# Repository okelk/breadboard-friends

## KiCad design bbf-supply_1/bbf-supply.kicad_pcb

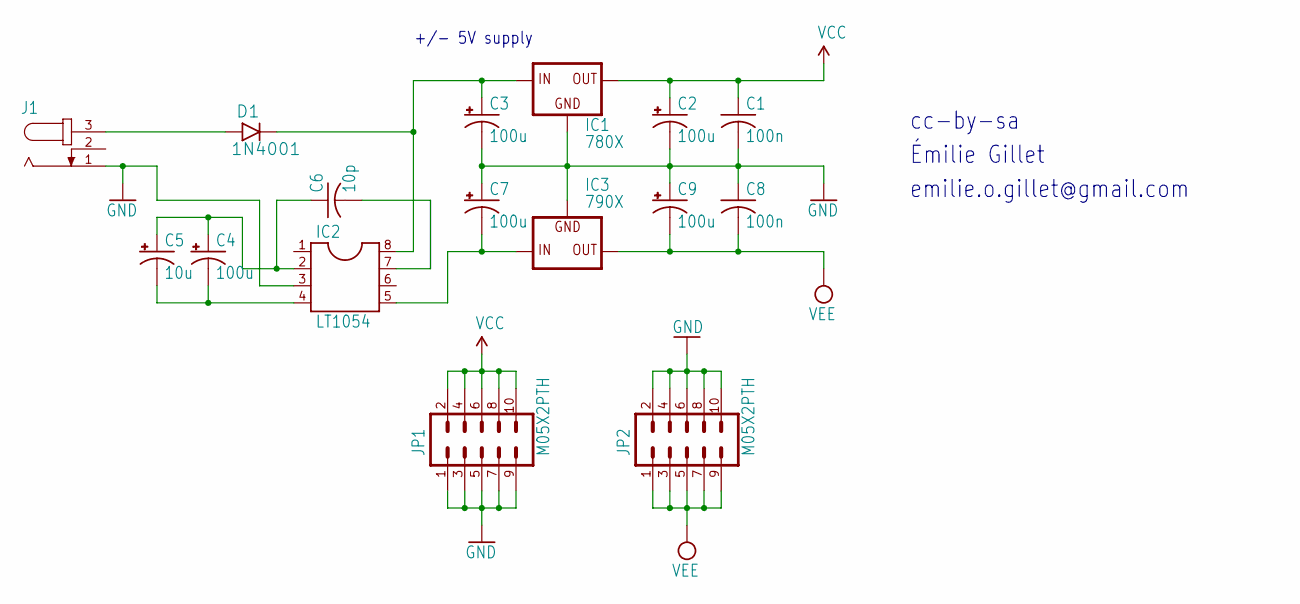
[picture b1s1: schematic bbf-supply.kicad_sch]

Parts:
C1, C8: 100n; C025-025X050
C2, C3, C7, C9: 100u; E2,5-7
C4: 100u; E2,5-6
C5: 10u; E2,5-5
C6: 10p; C025-025X050
D1: 1N4001; DO41-3
IC1: 780X; 78XXS
IC2: LT1054; DIL08
IC3: 790X; 79XXS
J1: JACK-PLUG2; SPC4078_BIG_HOLES
JP1, JP2: M05X2PTH; AVR_ICSP

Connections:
GND: C1.2, C2.-, C3.-, C7.+, C8.1, C9.+, IC1.GND, IC2.3, IC3.GND, J1.1, JP1.1, JP1.3, JP1.5, JP1.7, JP1.9, JP2.2, JP2.4, JP2.6, JP2.8, JP2.10
unnamed: D1.A, J1.3
unnamed: C3.+, D1.C, IC1.IN, IC2.8
unnamed: C4.+, C5.+, C6.1, IC2.2
unnamed: C4.-, C5.-, IC2.4
unnamed: C6.2, IC2.7
unnamed: C7.-, IC2.5, IC3.IN
VCC: C1.1, C2.+, IC1.OUT, JP1.2, JP1.4, JP1.6, JP1.8, JP1.10
VEE: C8.2, C9.-, IC3.OUT, JP2.1, JP2.3, JP2.5, JP2.7, JP2.9

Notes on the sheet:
Émilie Gillet
cc-by-sa
+/- 5V supply
emilie.o.gillet@gmail.com

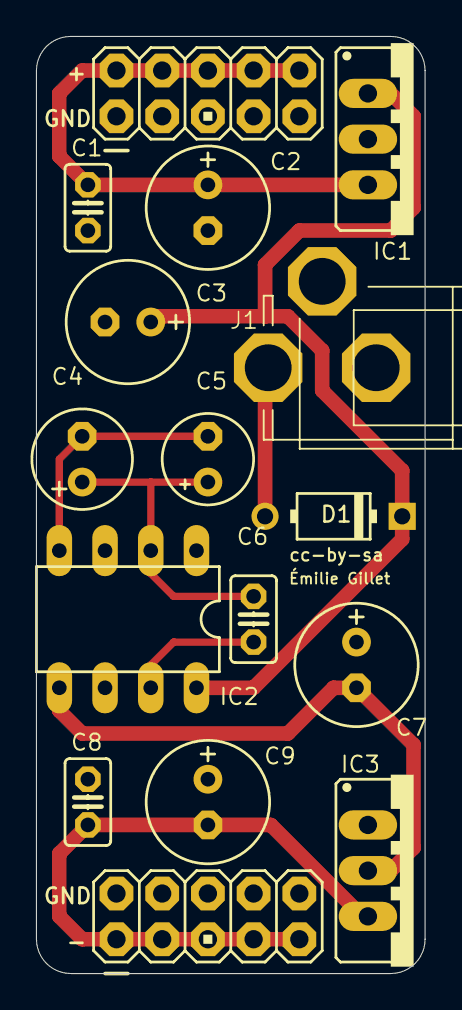
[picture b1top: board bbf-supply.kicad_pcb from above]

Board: 2 copper layers, 21.6 x 52.1 mm, 16 parts (0 on the bottom side), 9 nets.

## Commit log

2024-03-15 eagle xml / kicad conversion
